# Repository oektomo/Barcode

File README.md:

for PCB, source code for barcode
1. printer_mec it's printer mechanism PCB with FPC/FFC

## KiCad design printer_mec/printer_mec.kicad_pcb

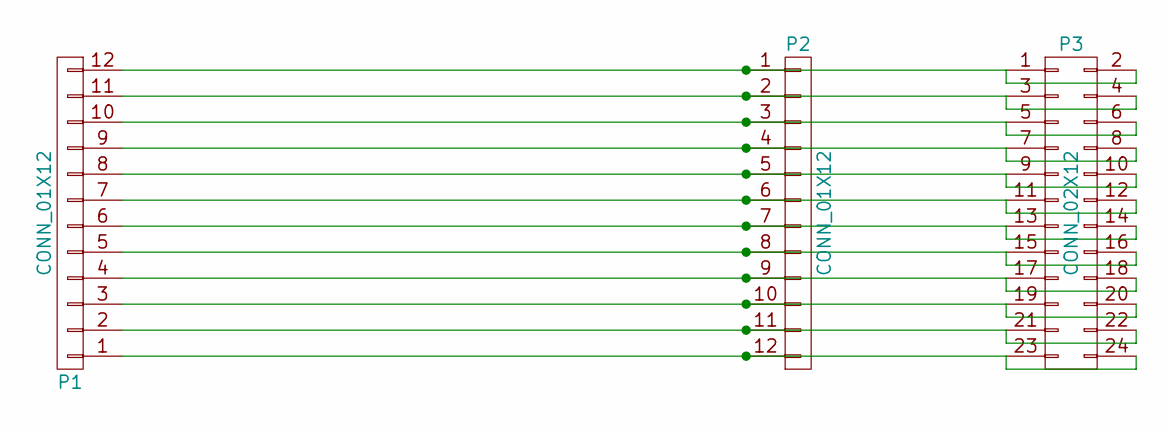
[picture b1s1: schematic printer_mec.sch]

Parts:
P1: CONN_01X12; Connectors_JST_SM12B-SRSS-TB
P2: CONN_01X12; Connector_Molex_PicoBlade_53398-1271
P3: CONN_02X12; Socket_Strip_Straight_2x12

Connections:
unnamed: P1.1, P2.12, P3.23, P3.24
unnamed: P1.2, P2.11, P3.21, P3.22
unnamed: P1.3, P2.10, P3.19, P3.20
unnamed: P1.4, P2.9, P3.17, P3.18
unnamed: P1.5, P2.8, P3.15, P3.16
unnamed: P1.6, P2.7, P3.13, P3.14
unnamed: P1.7, P2.6, P3.11, P3.12
unnamed: P1.8, P2.5, P3.9, P3.10
unnamed: P1.9, P2.4, P3.7, P3.8
unnamed: P1.10, P2.3, P3.5, P3.6
unnamed: P1.11, P2.2, P3.3, P3.4
unnamed: P1.12, P2.1, P3.1, P3.2

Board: 2 copper layers, 3 parts (0 on the bottom side), 12 nets, no tracks yet.
